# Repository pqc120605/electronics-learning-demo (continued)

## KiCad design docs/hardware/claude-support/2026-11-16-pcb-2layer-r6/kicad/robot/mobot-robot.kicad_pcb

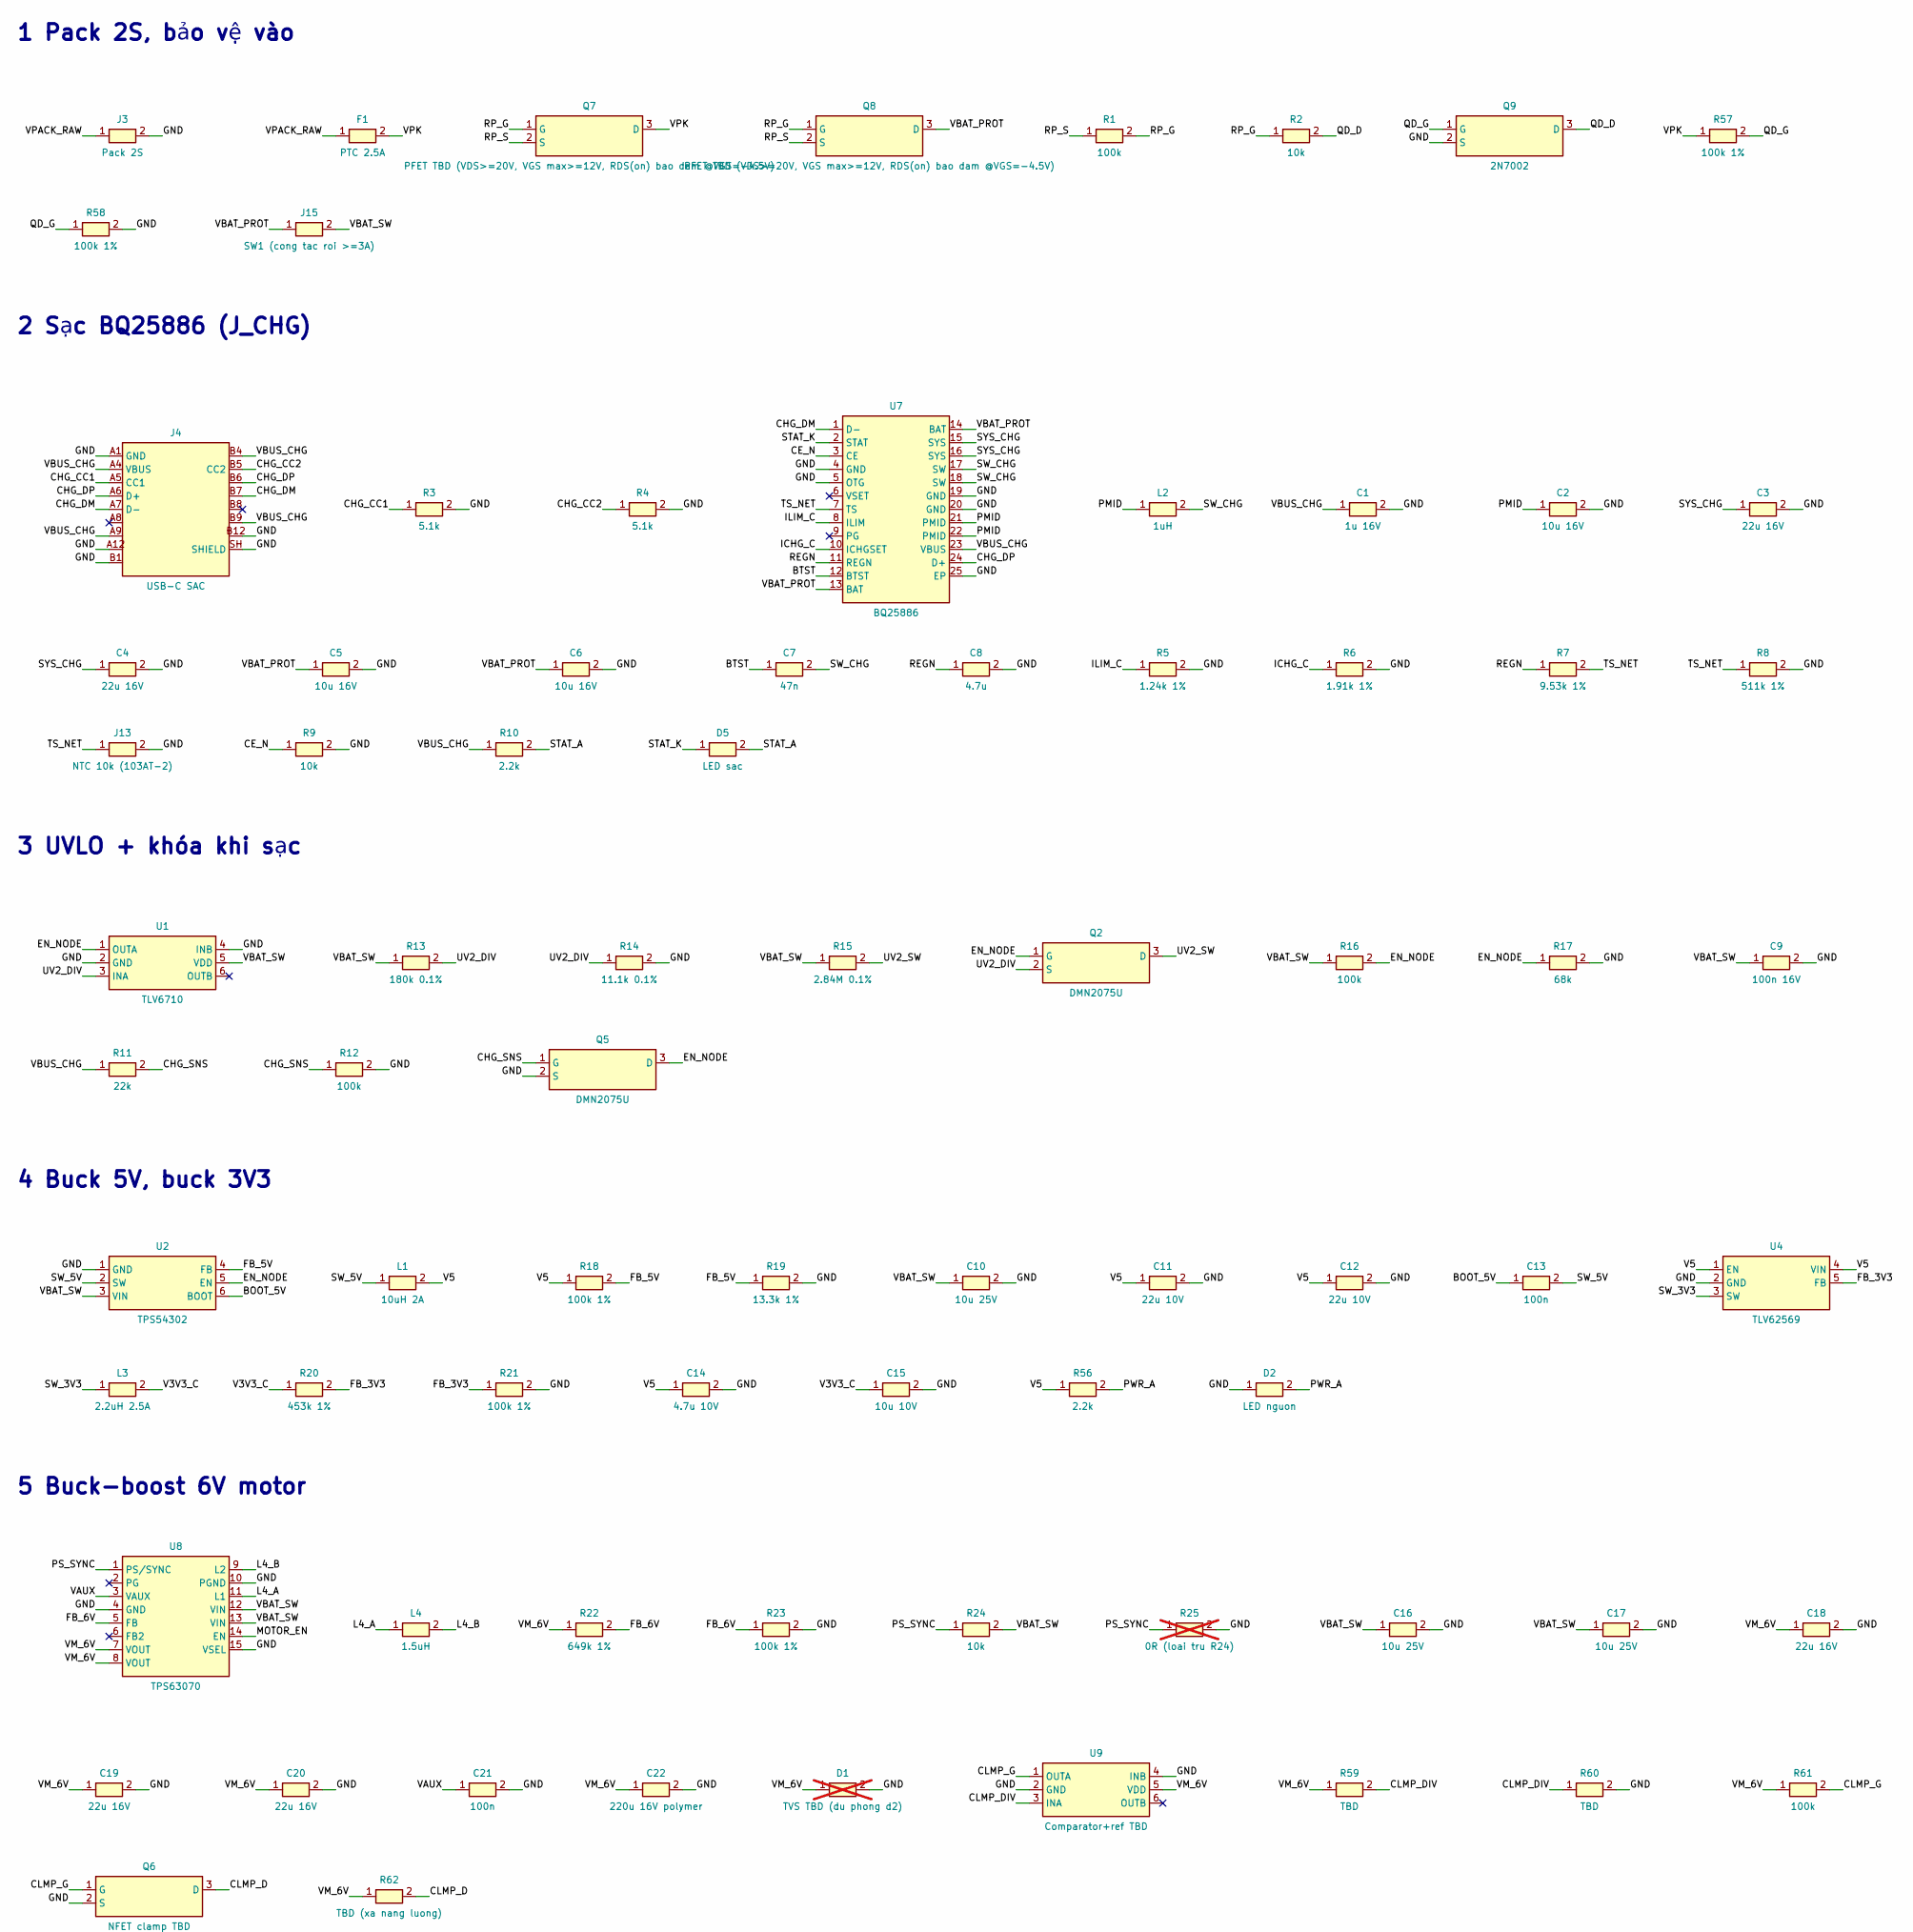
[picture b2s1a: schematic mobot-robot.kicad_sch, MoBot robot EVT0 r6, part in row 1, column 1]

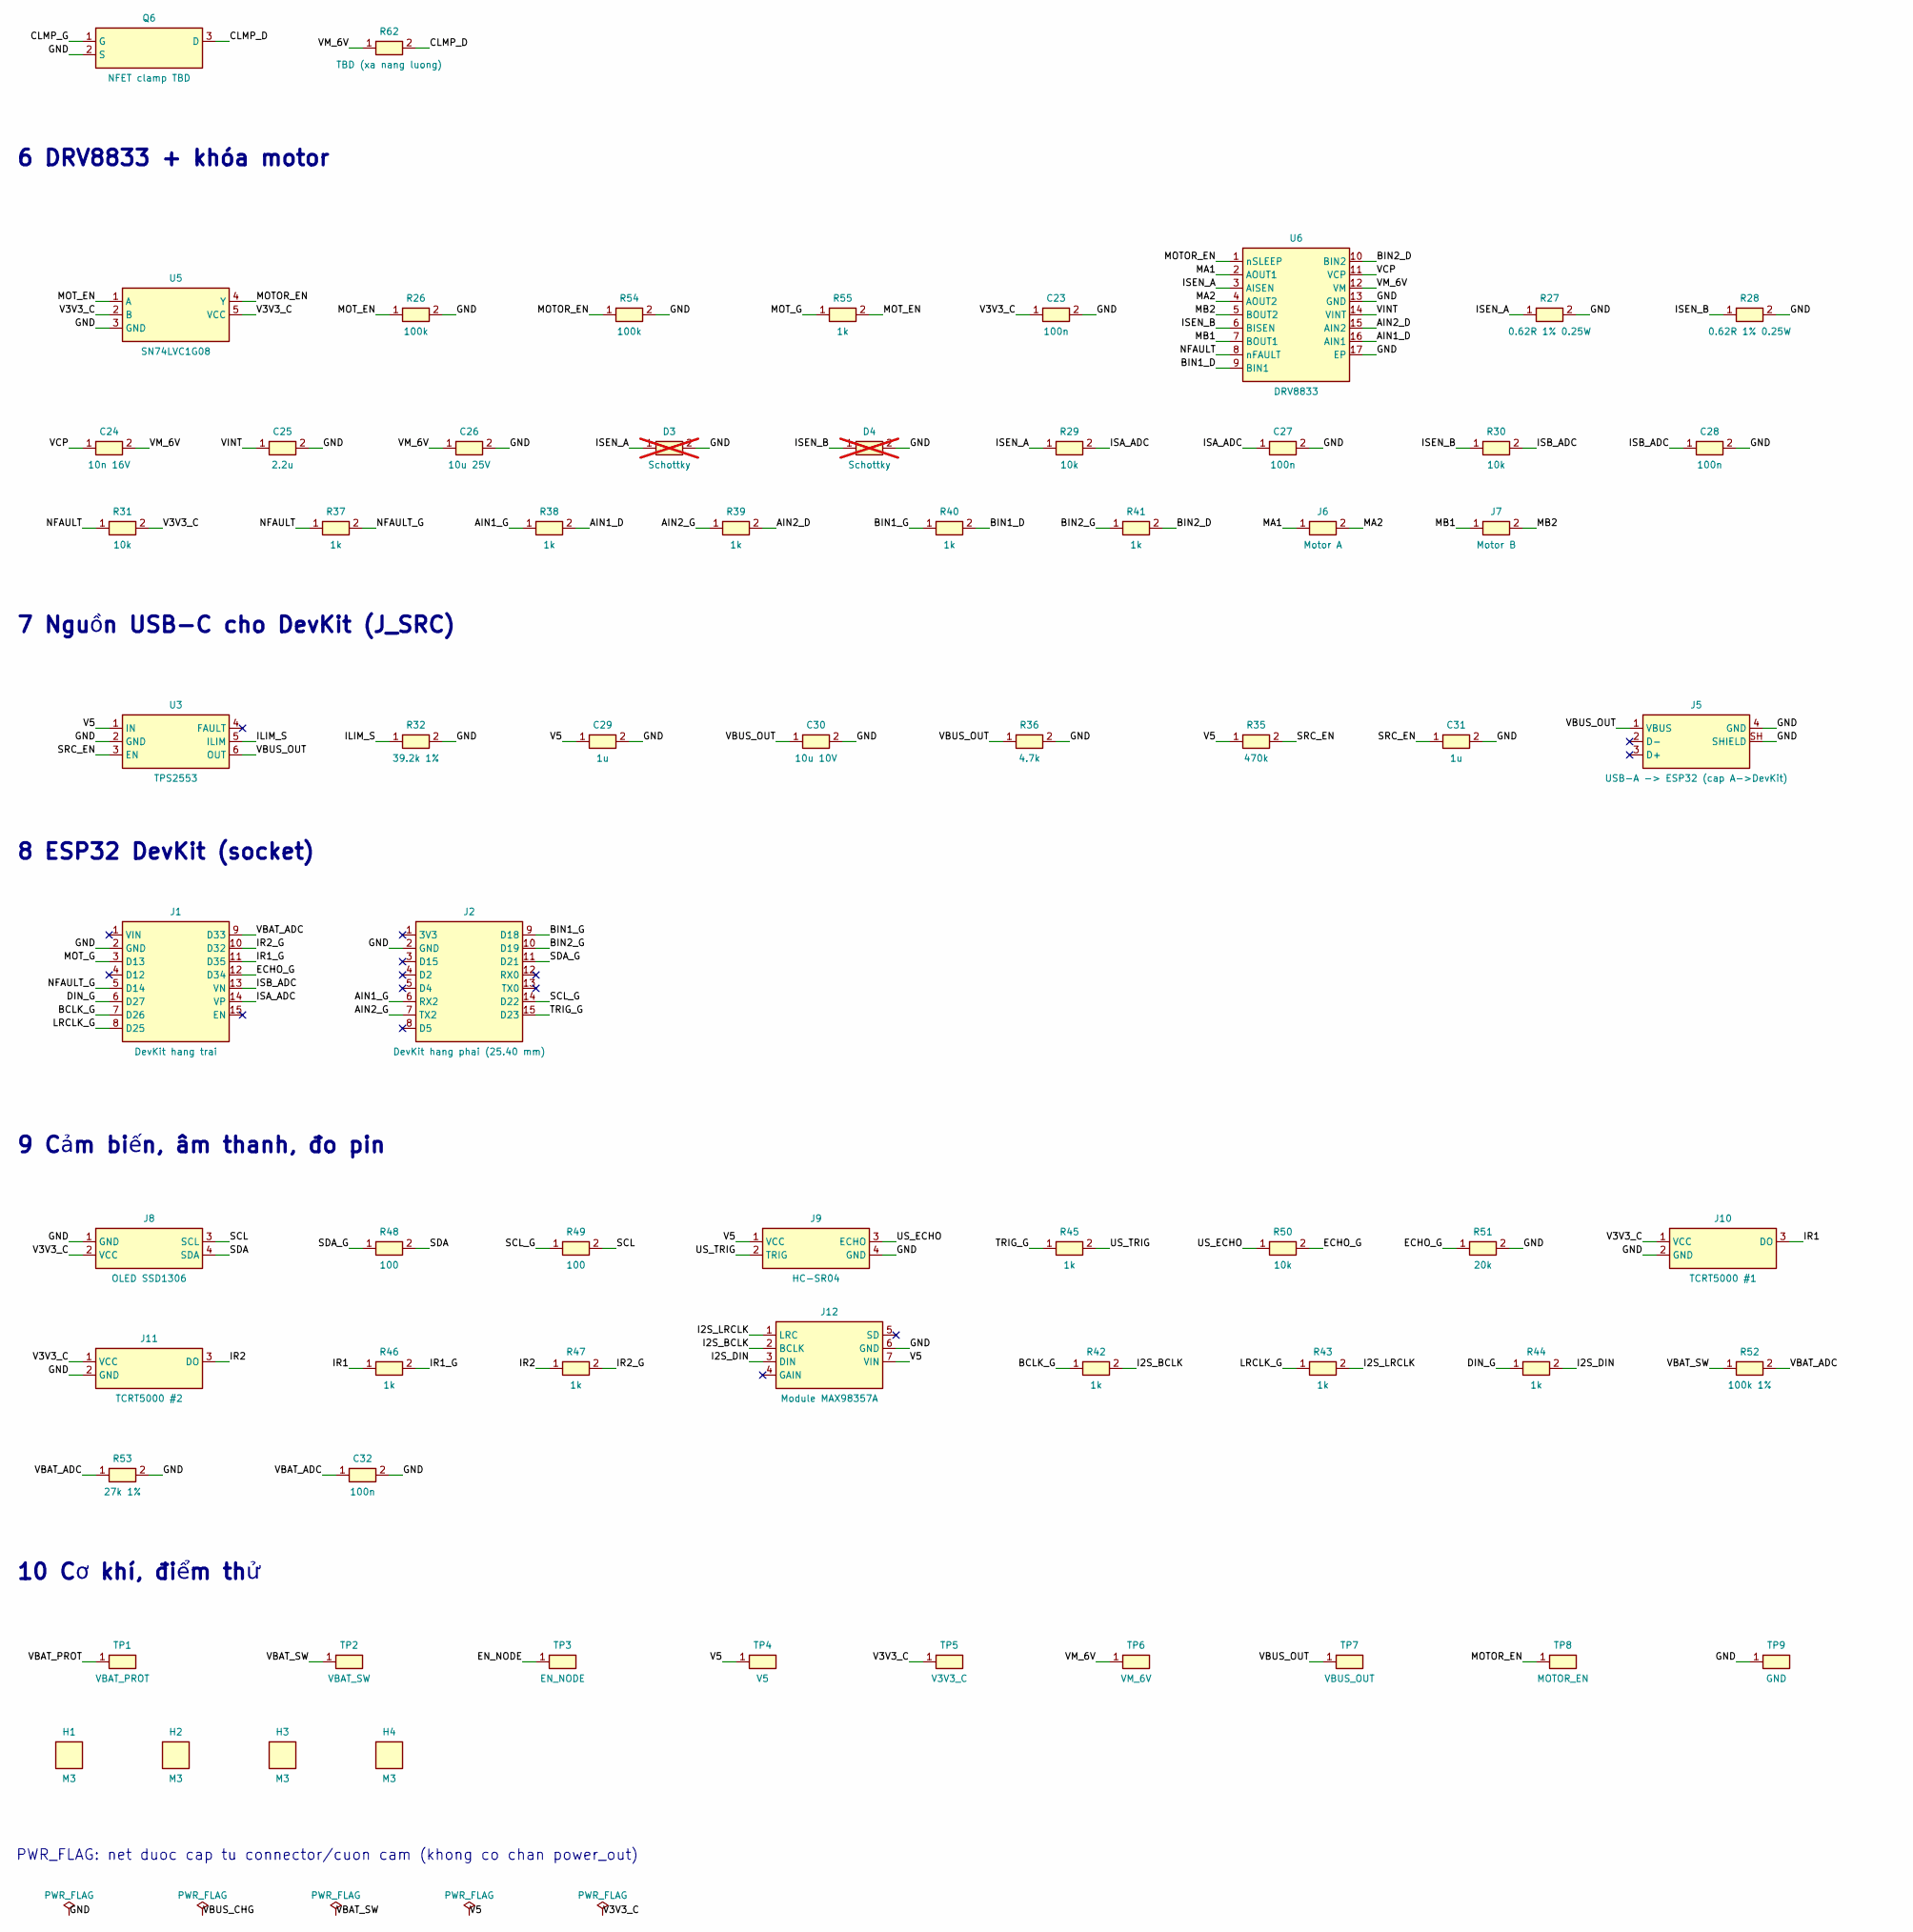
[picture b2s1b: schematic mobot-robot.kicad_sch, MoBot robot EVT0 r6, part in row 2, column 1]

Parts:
C1: 1u 16V; C_0603_1608Metric
C2, C5, C6: 10u 16V; C_0805_2012Metric
C3, C4, C18, C19, C20: 22u 16V; C_0805_2012Metric
C7: 47n; C_0603_1608Metric
C8: 4.7u; C_0603_1608Metric
C9: 100n 16V; C_0603_1608Metric
C10, C16, C17, C26: 10u 25V; C_0805_2012Metric
C11, C12: 22u 10V; C_0805_2012Metric
C13, C21, C23, C27, C28, C32: 100n; C_0603_1608Metric
C14: 4.7u 10V; C_0805_2012Metric
C15, C30: 10u 10V; C_0805_2012Metric
C22: 220u 16V polymer; CP_Elec_8x10
C24: 10n 16V; C_0603_1608Metric
C25: 2.2u; C_0603_1608Metric
C29, C31: 1u; C_0603_1608Metric
D1: TVS TBD (du phong d2); D_SMA; MPN TBD; not fitted
D2: LED nguon; LED_0603_1608Metric
D3, D4: Schottky; D_SOD-323; not fitted
D5: LED sac; LED_0603_1608Metric
F1: PTC 2.5A; Fuse_1812_4532Metric; MPN MF-MSMF250/16X
H1, H2, H3, H4: M3; MountingHole_3.2mm_M3
J1: DevKit hang trai; PinSocket_1x15_P2.54mm_Vertical
J2: DevKit hang phai (25.40 mm); PinSocket_1x15_P2.54mm_Vertical
J3: Pack 2S; JST_XH_B2B-XH-A_1x02_P2.50mm_Vertical; MPN B2B-XH-A
J4: USB-C SAC; USB_C_Receptacle_GCT_USB4105-xx-A_16P_TopMnt_Horizontal; MPN USB4105-GF-A
J5: USB-A -> ESP32 (cap A->DevKit); USB_A_Molex_67643_Horizontal; MPN Molex 67643 (suffix TBD)
J6: Motor A; JST_XH_B2B-XH-A_1x02_P2.50mm_Vertical; MPN B2B-XH-A
J7: Motor B; JST_XH_B2B-XH-A_1x02_P2.50mm_Vertical; MPN B2B-XH-A
J8: OLED SSD1306; PinSocket_1x04_P2.54mm_Vertical
J9: HC-SR04; PinSocket_1x04_P2.54mm_Vertical
J10: TCRT5000 #1; PinHeader_1x03_P2.54mm_Vertical
J11: TCRT5000 #2; PinHeader_1x03_P2.54mm_Vertical
J12: Module MAX98357A; PinSocket_1x07_P2.54mm_Vertical
J13: NTC 10k (103AT-2); JST_PH_B2B-PH-K_1x02_P2.00mm_Vertical; MPN B2B-PH-K-S
J15: SW1 (cong tac roi >=3A); JST_XH_B2B-XH-A_1x02_P2.50mm_Vertical; MPN B2B-XH-A
L1: 10uH 2A; L_Taiyo-Yuden_NR-50xx
L2: 1uH; L_Vishay_IHLP-2525; MPN IHLP2525CZER1R0M01
L3: 2.2uH 2.5A; L_Changjiang_FNR4030S
L4: 1.5uH; L_Changjiang_FNR4020S; MPN XFL4020-152ME
Q2, Q5: DMN2075U; SOT-23; MPN DMN2075U-7
Q6: NFET clamp TBD; SOT-23; MPN TBD
Q7, Q8: PFET TBD (VDS>=20V, VGS max>=12V, RDS(on) bao dam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; SOT-23; MPN TBD
Q9: 2N7002; SOT-23; MPN 2N7002
R1, R12, R16, R26, R54, R61: 100k; R_0603_1608Metric
R2, R9, R24, R29, R30, R31, R50: 10k; R_0603_1608Metric
R3, R4: 5.1k; R_0603_1608Metric
R5: 1.24k 1%; R_0603_1608Metric
R6: 1.91k 1%; R_0603_1608Metric
R7: 9.53k 1%; R_0603_1608Metric
R8: 511k 1%; R_0603_1608Metric
R10, R56: 2.2k; R_0603_1608Metric
R11: 22k; R_0603_1608Metric
R13: 180k 0.1%; R_0603_1608Metric
R14: 11.1k 0.1%; R_0603_1608Metric
R15: 2.84M 0.1%; R_0603_1608Metric
R17: 68k; R_0603_1608Metric
R18, R21, R23, R52, R57, R58: 100k 1%; R_0603_1608Metric
R19: 13.3k 1%; R_0603_1608Metric
R20: 453k 1%; R_0603_1608Metric
R22: 649k 1%; R_0603_1608Metric
R25: 0R (loai tru R24); R_0603_1608Metric; not fitted
R27, R28: 0.62R 1% 0.25W; R_1206_3216Metric
R32: 39.2k 1%; R_0603_1608Metric
R35: 470k; R_0603_1608Metric
R36: 4.7k; R_0603_1608Metric
R37, R38, R39, R40, R41, R42, R43, R44, R45, R46, R47, R55: 1k; R_0603_1608Metric
R48, R49: 100; R_0603_1608Metric
R51: 20k; R_0603_1608Metric
R53: 27k 1%; R_0603_1608Metric
R59, R60: TBD; R_0603_1608Metric
R62: TBD (xa nang luong); R_2512_6332Metric
TP1: VBAT_PROT; TestPoint_Pad_D1.5mm
TP2: VBAT_SW; TestPoint_Pad_D1.5mm
TP3: EN_NODE; TestPoint_Pad_D1.5mm
TP4: V5; TestPoint_Pad_D1.5mm
TP5: V3V3_C; TestPoint_Pad_D1.5mm
TP6: VM_6V; TestPoint_Pad_D1.5mm
TP7: VBUS_OUT; TestPoint_Pad_D1.5mm
TP8: MOTOR_EN; TestPoint_Pad_D1.5mm
TP9: GND; TestPoint_Pad_D1.5mm
U1: TLV6710; TSOT-23-6; MPN TLV6710DDCR
U2: TPS54302; SOT-23-6; MPN TPS54302DDCR
U3: TPS2553; SOT-23-6; MPN TPS2553DBVR
U4: TLV62569; SOT-23-5; MPN TLV62569DBVR
U5: SN74LVC1G08; SOT-23-5; MPN SN74LVC1G08DBVR
U6: DRV8833; HTSSOP-16-1EP_4.4x5mm_P0.65mm_EP3.4x5mm_Mask2.46x2.31mm; MPN DRV8833PWPR
U7: BQ25886; VQFN-24-1EP_4x4mm_P0.5mm_EP2.45x2.45mm; MPN BQ25886RGER
U8: TPS63070; Texas_RNM0015A_VQFN-15_2.5x3mm; MPN TPS63070RNMR
U9: Comparator+ref TBD; TSOT-23-6; MPN TBD

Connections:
/AIN1_D: R38.2, U6.16 (AIN1)
/AIN1_G: J2.6 (RX2), R38.1
/AIN2_D: R39.2, U6.15 (AIN2)
/AIN2_G: J2.7 (TX2), R39.1
/BCLK_G: J1.7 (D26), R42.1
/BIN1_D: R40.2, U6.9 (BIN1)
/BIN1_G: J2.9 (D18), R40.1
/BIN2_D: R41.2, U6.10 (BIN2)
/BIN2_G: J2.10 (D19), R41.1
/BOOT_5V: C13.1, U2.6 (BOOT)
/BTST: C7.1, U7.12 (BTST)
/CE_N: R9.1, U7.3 (CE)
/CHG_CC1: J4.A5 (CC1), R3.1
/CHG_CC2: J4.B5 (CC2), R4.1
/CHG_DM: J4.A7 (D-), J4.B7, U7.1 (D-)
/CHG_DP: J4.A6 (D+), J4.B6, U7.24 (D+)
/CHG_SNS: Q5.1 (G), R11.2, R12.1
/CLMP_D: Q6.3 (D), R62.2
/CLMP_DIV: R59.2, R60.1, U9.3 (INA)
/CLMP_G: Q6.1 (G), R61.2, U9.1 (OUTA)
/DIN_G: J1.6 (D27), R44.1
/ECHO_G: J1.12 (D34), R50.2, R51.1
/EN_NODE: Q2.1 (G), Q5.3 (D), R16.2, R17.1, TP3.1, U1.1 (OUTA), U2.5 (EN)
/FB_3V3: R20.2, R21.1, U4.5 (FB)
/FB_5V: R18.2, R19.1, U2.4 (FB)
/FB_6V: R22.2, R23.1, U8.5 (FB)
/GND: C1.2, C2.2, C3.2, C4.2, C5.2, C6.2, C8.2, C9.2, C10.2, C11.2, C12.2, C14.2, C15.2, C16.2, C17.2, C18.2, C19.2, C20.2, C21.2, C22.2 (-), C23.2, C25.2, C26.2, C27.2, C28.2, C29.2, C30.2, C31.2, C32.2, D1.2 (A), D2.1 (K), D3.2 (A), D4.2 (A), J1.2 (GND), J2.2 (GND), J3.2 (-), J4.A1 (GND), J4.A12, J4.B1, J4.B12, J4.SH (SHIELD), J5.4 (GND), J5.SH (SHIELD), J8.1 (GND), J9.4 (GND), J10.2 (GND), J11.2 (GND), J12.6 (GND), J13.2, Q5.2 (S), Q6.2 (S), Q9.2 (S), R3.2, R4.2, R5.2, R6.2, R8.2, R9.2, R12.2, R14.2, R17.2, R19.2, R21.2, R23.2, R25.2, R26.2, R27.2, R28.2, R32.2, R36.2, R51.2, R53.2, R54.2, R58.2, R60.2, TP9.1, U1.2 (GND), U1.4 (INB), U2.1 (GND), U3.2 (GND), U4.2 (GND), U5.3 (GND), U6.13 (GND), U6.17 (EP), U7.4 (GND), U7.5 (OTG), U7.19 (GND), U7.20 (GND), U7.25 (EP), U8.4 (GND), U8.10 (PGND), U8.15 (VSEL), U9.2 (GND), U9.4 (INB)
/I2S_BCLK: J12.2 (BCLK), R42.2
/I2S_DIN: J12.3 (DIN), R44.2
/I2S_LRCLK: J12.1 (LRC), R43.2
/ICHG_C: R6.1, U7.10 (ICHGSET)
/ILIM_C: R5.1, U7.8 (ILIM)
/ILIM_S: R32.1, U3.5 (ILIM)
/IR1: J10.3 (DO), R46.1
/IR1_G: J1.11 (D35), R46.2
/IR2: J11.3 (DO), R47.1
/IR2_G: J1.10 (D32), R47.2
/ISA_ADC: C27.1, J1.14 (VP), R29.2
/ISB_ADC: C28.1, J1.13 (VN), R30.2
/ISEN_A: D3.1 (K), R27.1, R29.1, U6.3 (AISEN)
/ISEN_B: D4.1 (K), R28.1, R30.1, U6.6 (BISEN)
/L4_A: L4.1, U8.11 (L1)
/L4_B: L4.2, U8.9 (L2)
/LRCLK_G: J1.8 (D25), R43.1
/MA1: J6.1, U6.2 (AOUT1)
/MA2: J6.2, U6.4 (AOUT2)
/MB1: J7.1, U6.7 (BOUT1)
/MB2: J7.2, U6.5 (BOUT2)
/MOTOR_EN: R54.1, TP8.1, U5.4 (Y), U6.1 (nSLEEP), U8.14 (EN)
/MOT_EN: R26.1, R55.2, U5.1 (A)
/MOT_G: J1.3 (D13), R55.1
/NFAULT: R31.1, R37.1, U6.8 (nFAULT)
/NFAULT_G: J1.5 (D14), R37.2
/PMID: C2.1, L2.1, U7.21 (PMID), U7.22 (PMID)
/PS_SYNC: R24.1, R25.1, U8.1 (PS/SYNC)
/PWR_A: D2.2 (A), R56.2
/QD_D: Q9.3 (D), R2.2
/QD_G: Q9.1 (G), R57.2, R58.1
/REGN: C8.1, R7.1, U7.11 (REGN)
/RP_G: Q7.1 (G), Q8.1 (G), R1.2, R2.1
/RP_S: Q7.2 (S), Q8.2 (S), R1.1
/SCL: J8.3 (SCL), R49.2
/SCL_G: J2.14 (D22), R49.1
/SDA: J8.4 (SDA), R48.2
/SDA_G: J2.11 (D21), R48.1
/SRC_EN: C31.1, R35.2, U3.3 (EN)
/STAT_A: D5.2 (A), R10.2
/STAT_K: D5.1 (K), U7.2 (STAT)
/SW_3V3: L3.1, U4.3 (SW)
/SW_5V: C13.2, L1.1, U2.2 (SW)
/SW_CHG: C7.2, L2.2, U7.17 (SW), U7.18 (SW)
/SYS_CHG: C3.1, C4.1, U7.15 (SYS), U7.16 (SYS)
/TRIG_G: J2.15 (D23), R45.1
/TS_NET: J13.1, R7.2, R8.1, U7.7 (TS)
/US_ECHO: J9.3 (ECHO), R50.1
/US_TRIG: J9.2 (TRIG), R45.2
/UV2_DIV: Q2.2 (S), R13.2, R14.1, U1.3 (INA)
/UV2_SW: Q2.3 (D), R15.2
/V3V3_C: C15.1, C23.1, J8.2 (VCC), J10.1 (VCC), J11.1 (VCC), L3.2, R20.1, R31.2, TP5.1, U5.2 (B), U5.5 (VCC)
/V5: C11.1, C12.1, C14.1, C29.1, J9.1 (VCC), J12.7 (VIN), L1.2, R18.1, R35.1, R56.1, TP4.1, U3.1 (IN), U4.1 (EN), U4.4 (VIN)
/VAUX: C21.1, U8.3 (VAUX)
/VBAT_ADC: C32.1, J1.9 (D33), R52.2, R53.1
/VBAT_PROT: C5.1, C6.1, J15.1 (IN), Q8.3 (D), TP1.1, U7.13 (BAT), U7.14 (BAT)
/VBAT_SW: C9.1, C10.1, C16.1, C17.1, J15.2 (OUT), R13.1, R15.1, R16.1, R24.2, R52.1, TP2.1, U1.5 (VDD), U2.3 (VIN), U8.12 (VIN), U8.13 (VIN)
/VBUS_CHG: C1.1, J4.A4 (VBUS), J4.A9, J4.B4, J4.B9, R10.1, R11.1, U7.23 (VBUS)
/VBUS_OUT: C30.1, J5.1 (VBUS), R36.1, TP7.1, U3.6 (OUT)
/VCP: C24.1, U6.11 (VCP)
/VINT: C25.1, U6.14 (VINT)
/VM_6V: C18.1, C19.1, C20.1, C22.1 (+), C24.2, C26.1, D1.1 (K), R22.1, R59.1, R61.1, R62.1, TP6.1, U6.12 (VM), U8.7 (VOUT), U8.8 (VOUT), U9.5 (VDD)
/VPACK_RAW: F1.1, J3.1 (+)
/VPK: F1.2, Q7.3 (D), R57.1

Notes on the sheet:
1 Pack 2S, bảo vệ vào
2 Sạc BQ25886 (J_CHG)
3 UVLO + khóa khi sạc
4 Buck 5V, buck 3V3
5 Buck-boost 6V motor
6 DRV8833 + khóa motor
7 Nguồn USB-C cho DevKit (J_SRC)
8 ESP32 DevKit (socket)
9 Cảm biến, âm thanh, đo pin
10 Cơ khí, điểm thử
PWR_FLAG: net duoc cap tu connector/cuon cam (khong co chan power_out)

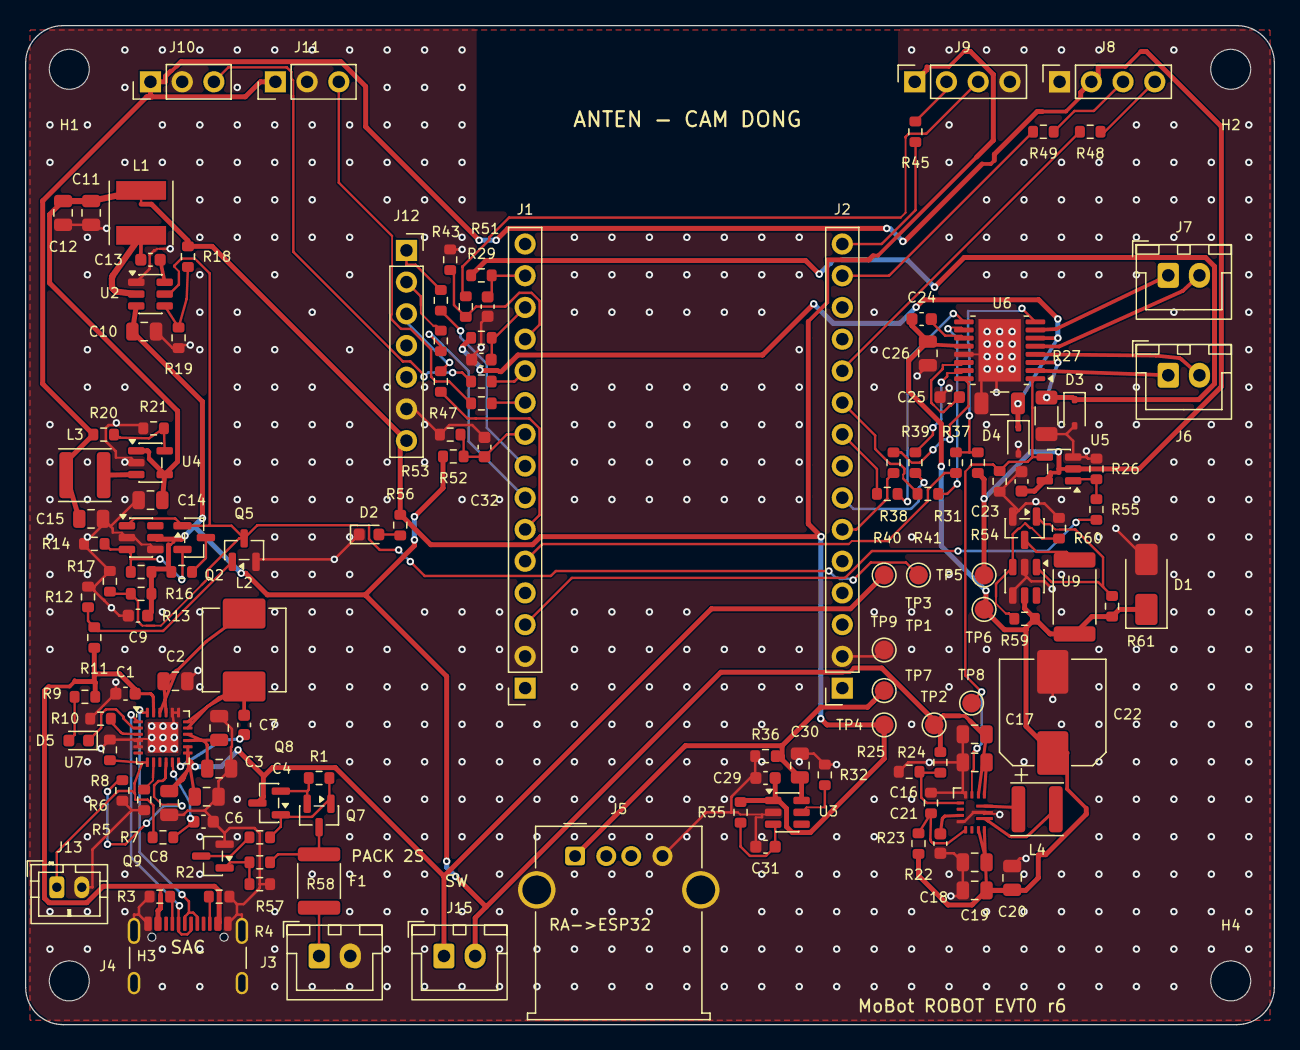
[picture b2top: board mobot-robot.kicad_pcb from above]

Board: 2 copper layers, 100.0 x 80.0 mm, 144 parts (0 on the bottom side), 91 nets.

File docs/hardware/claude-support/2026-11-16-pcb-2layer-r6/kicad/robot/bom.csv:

"Reference","Value","Footprint","MPN","QUANTITY","DNP"
"C1","1u 16V","Capacitor_SMD:C_0603_1608Metric","","1",""
"C2,C5,C6","10u 16V","Capacitor_SMD:C_0805_2012Metric","","3",""
"C3,C4,C18-C20","22u 16V","Capacitor_SMD:C_0805_2012Metric","","5",""
"C7","47n","Capacitor_SMD:C_0603_1608Metric","","1",""
"C8","4.7u","Capacitor_SMD:C_0603_1608Metric","","1",""
"C9","100n 16V","Capacitor_SMD:C_0603_1608Metric","","1",""
"C10,C16,C17,C26","10u 25V","Capacitor_SMD:C_0805_2012Metric","","4",""
"C11,C12","22u 10V","Capacitor_SMD:C_0805_2012Metric","","2",""
"C13,C21,C23,C27,C28,C32","100n","Capacitor_SMD:C_0603_1608Metric","","6",""
"C14","4.7u 10V","Capacitor_SMD:C_0805_2012Metric","","1",""
"C15,C30","10u 10V","Capacitor_SMD:C_0805_2012Metric","","2",""
"C22","220u 16V polymer","Capacitor_SMD:CP_Elec_8x10","","1",""
"C24","10n 16V","Capacitor_SMD:C_0603_1608Metric","","1",""
"C25","2.2u","Capacitor_SMD:C_0603_1608Metric","","1",""
"C29,C31","1u","Capacitor_SMD:C_0603_1608Metric","","2",""
"D1","TVS TBD (du phong d2)","Diode_SMD:D_SMA","TBD","1","DNP"
"D2","LED nguon","LED_SMD:LED_0603_1608Metric","","1",""
"D3,D4","Schottky","Diode_SMD:D_SOD-323","","2","DNP"
"D5","LED sac","LED_SMD:LED_0603_1608Metric","","1",""
"F1","PTC 2.5A","Fuse:Fuse_1812_4532Metric","MF-MSMF250/16X","1",""
"J1","DevKit hang trai","Connector_PinSocket_2.54mm:PinSocket_1x15_P2.54mm_Vertical","","1",""
"J2","DevKit hang phai (25.40 mm)","Connector_PinSocket_2.54mm:PinSocket_1x15_P2.54mm_Vertical","","1",""
"J3","Pack 2S","Connector_JST:JST_XH_B2B-XH-A_1x02_P2.50mm_Vertical","B2B-XH-A","1",""
"J4","USB-C SAC","Connector_USB:USB_C_Receptacle_GCT_USB4105-xx-A_16P_TopMnt_Horizontal","USB4105-GF-A","1",""
"J5","USB-A -> ESP32 (cap A->DevKit)","Connector_USB:USB_A_Molex_67643_Horizontal","Molex 67643 (suffix TBD)","1",""
"J6","Motor A","Connector_JST:JST_XH_B2B-XH-A_1x02_P2.50mm_Vertical","B2B-XH-A","1",""
"J7","Motor B","Connector_JST:JST_XH_B2B-XH-A_1x02_P2.50mm_Vertical","B2B-XH-A","1",""
"J8","OLED SSD1306","Connector_PinSocket_2.54mm:PinSocket_1x04_P2.54mm_Vertical","","1",""
"J9","HC-SR04","Connector_PinSocket_2.54mm:PinSocket_1x04_P2.54mm_Vertical","","1",""
"J10","TCRT5000 #1","Connector_PinHeader_2.54mm:PinHeader_1x03_P2.54mm_Vertical","","1",""
"J11","TCRT5000 #2","Connector_PinHeader_2.54mm:PinHeader_1x03_P2.54mm_Vertical","","1",""
"J12","Module MAX98357A","Connector_PinSocket_2.54mm:PinSocket_1x07_P2.54mm_Vertical","","1",""
"J13","NTC 10k (103AT-2)","Connector_JST:JST_PH_B2B-PH-K_1x02_P2.00mm_Vertical","B2B-PH-K-S","1",""
"J15","SW1 (cong tac roi >=3A)","Connector_JST:JST_XH_B2B-XH-A_1x02_P2.50mm_Vertical","B2B-XH-A","1",""
"L1","10uH 2A","Inductor_SMD:L_Taiyo-Yuden_NR-50xx","","1",""
"L2","1uH","Inductor_SMD:L_Vishay_IHLP-2525","IHLP2525CZER1R0M01","1",""
"L3","2.2uH 2.5A","Inductor_SMD:L_Changjiang_FNR4030S","","1",""
"L4","1.5uH","Inductor_SMD:L_Changjiang_FNR4020S","XFL4020-152ME","1",""
"Q2,Q5","DMN2075U","Package_TO_SOT_SMD:SOT-23","DMN2075U-7","2",""
"Q6","NFET clamp TBD","Package_TO_SOT_SMD:SOT-23","TBD","1",""
"Q7,Q8","PFET TBD (VDS>=20V, VGS max>=12V, RDS(on) bao dam @VGS=-4.5V)","Package_TO_SOT_SMD:SOT-23","TBD","2",""
"Q9","2N7002","Package_TO_SOT_SMD:SOT-23","2N7002","1",""
"R1,R12,R16,R26,R54,R61","100k","Resistor_SMD:R_0603_1608Metric","","6",""
"R2,R9,R24,R29-R31,R50","10k","Resistor_SMD:R_0603_1608Metric","","7",""
"R3,R4","5.1k","Resistor_SMD:R_0603_1608Metric","","2",""
"R5","1.24k 1%","Resistor_SMD:R_0603_1608Metric","","1",""
"R6","1.91k 1%","Resistor_SMD:R_0603_1608Metric","","1",""
"R7","9.53k 1%","Resistor_SMD:R_0603_1608Metric","","1",""
"R8","511k 1%","Resistor_SMD:R_0603_1608Metric","","1",""
"R10,R56","2.2k","Resistor_SMD:R_0603_1608Metric","","2",""
"R11","22k","Resistor_SMD:R_0603_1608Metric","","1",""
"R13","180k 0.1%","Resistor_SMD:R_0603_1608Metric","","1",""
"R14","11.1k 0.1%","Resistor_SMD:R_0603_1608Metric","","1",""
"R15","2.84M 0.1%","Resistor_SMD:R_0603_1608Metric","","1",""
"R17","68k","Resistor_SMD:R_0603_1608Metric","","1",""
"R18,R21,R23,R52,R57,R58","100k 1%","Resistor_SMD:R_0603_1608Metric","","6",""
"R19","13.3k 1%","Resistor_SMD:R_0603_1608Metric","","1",""
"R20","453k 1%","Resistor_SMD:R_0603_1608Metric","","1",""
"R22","649k 1%","Resistor_SMD:R_0603_1608Metric","","1",""
"R25","0R (loai tru R24)","Resistor_SMD:R_0603_1608Metric","","1","DNP"
"R27,R28","0.62R 1% 0.25W","Resistor_SMD:R_1206_3216Metric","","2",""
"R32","39.2k 1%","Resistor_SMD:R_0603_1608Metric","","1",""
"R35","470k","Resistor_SMD:R_0603_1608Metric","","1",""
"R36","4.7k","Resistor_SMD:R_0603_1608Metric","","1",""
"R37-R47,R55","1k","Resistor_SMD:R_0603_1608Metric","","12",""
"R48,R49","100","Resistor_SMD:R_0603_1608Metric","","2",""
"R51","20k","Resistor_SMD:R_0603_1608Metric","","1",""
"R53","27k 1%","Resistor_SMD:R_0603_1608Metric","","1",""
"R59,R60","TBD","Resistor_SMD:R_0603_1608Metric","","2",""
"R62","TBD (xa nang luong)","Resistor_SMD:R_2512_6332Metric","","1",""
"U1","TLV6710","Package_TO_SOT_SMD:TSOT-23-6","TLV6710DDCR","1",""
"U2","TPS54302","Package_TO_SOT_SMD:SOT-23-6","TPS54302DDCR","1",""
"U3","TPS2553","Package_TO_SOT_SMD:SOT-23-6","TPS2553DBVR","1",""
"U4","TLV62569","Package_TO_SOT_SMD:SOT-23-5","TLV62569DBVR","1",""
"U5","SN74LVC1G08","Package_TO_SOT_SMD:SOT-23-5","SN74LVC1G08DBVR","1",""
"U6","DRV8833","Package_SO:HTSSOP-16-1EP_4.4x5mm_P0.65mm_EP3.4x5mm_Mask2.46x2.31mm","DRV8833PWPR","1",""
"U7","BQ25886","Package_DFN_QFN:VQFN-24-1EP_4x4mm_P0.5mm_EP2.45x2.45mm","BQ25886RGER","1",""
"U8","TPS63070","mobot:Texas_RNM0015A_VQFN-15_2.5x3mm","TPS63070RNMR","1",""
"U9","Comparator+ref TBD","Package_TO_SOT_SMD:TSOT-23-6","TBD","1",""

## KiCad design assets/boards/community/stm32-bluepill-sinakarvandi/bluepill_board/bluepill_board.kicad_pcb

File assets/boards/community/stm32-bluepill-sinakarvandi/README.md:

# PCB Designs

My random PCB designs using [KiCad](https://www.kicad.org/).

- **Blue Pill Board**

  Custom PCB design for STM32 "Blue Pill" development board.

- **ESP32-S3 Board**

  Schematic and layout for ESP32-S3-based design.

- **ESP32 WROOM Board**

  PCB based on ESP32-WROOM module.

- **LED Blinker**

  Simple circuit for testing LEDs and basic PCB workflow.

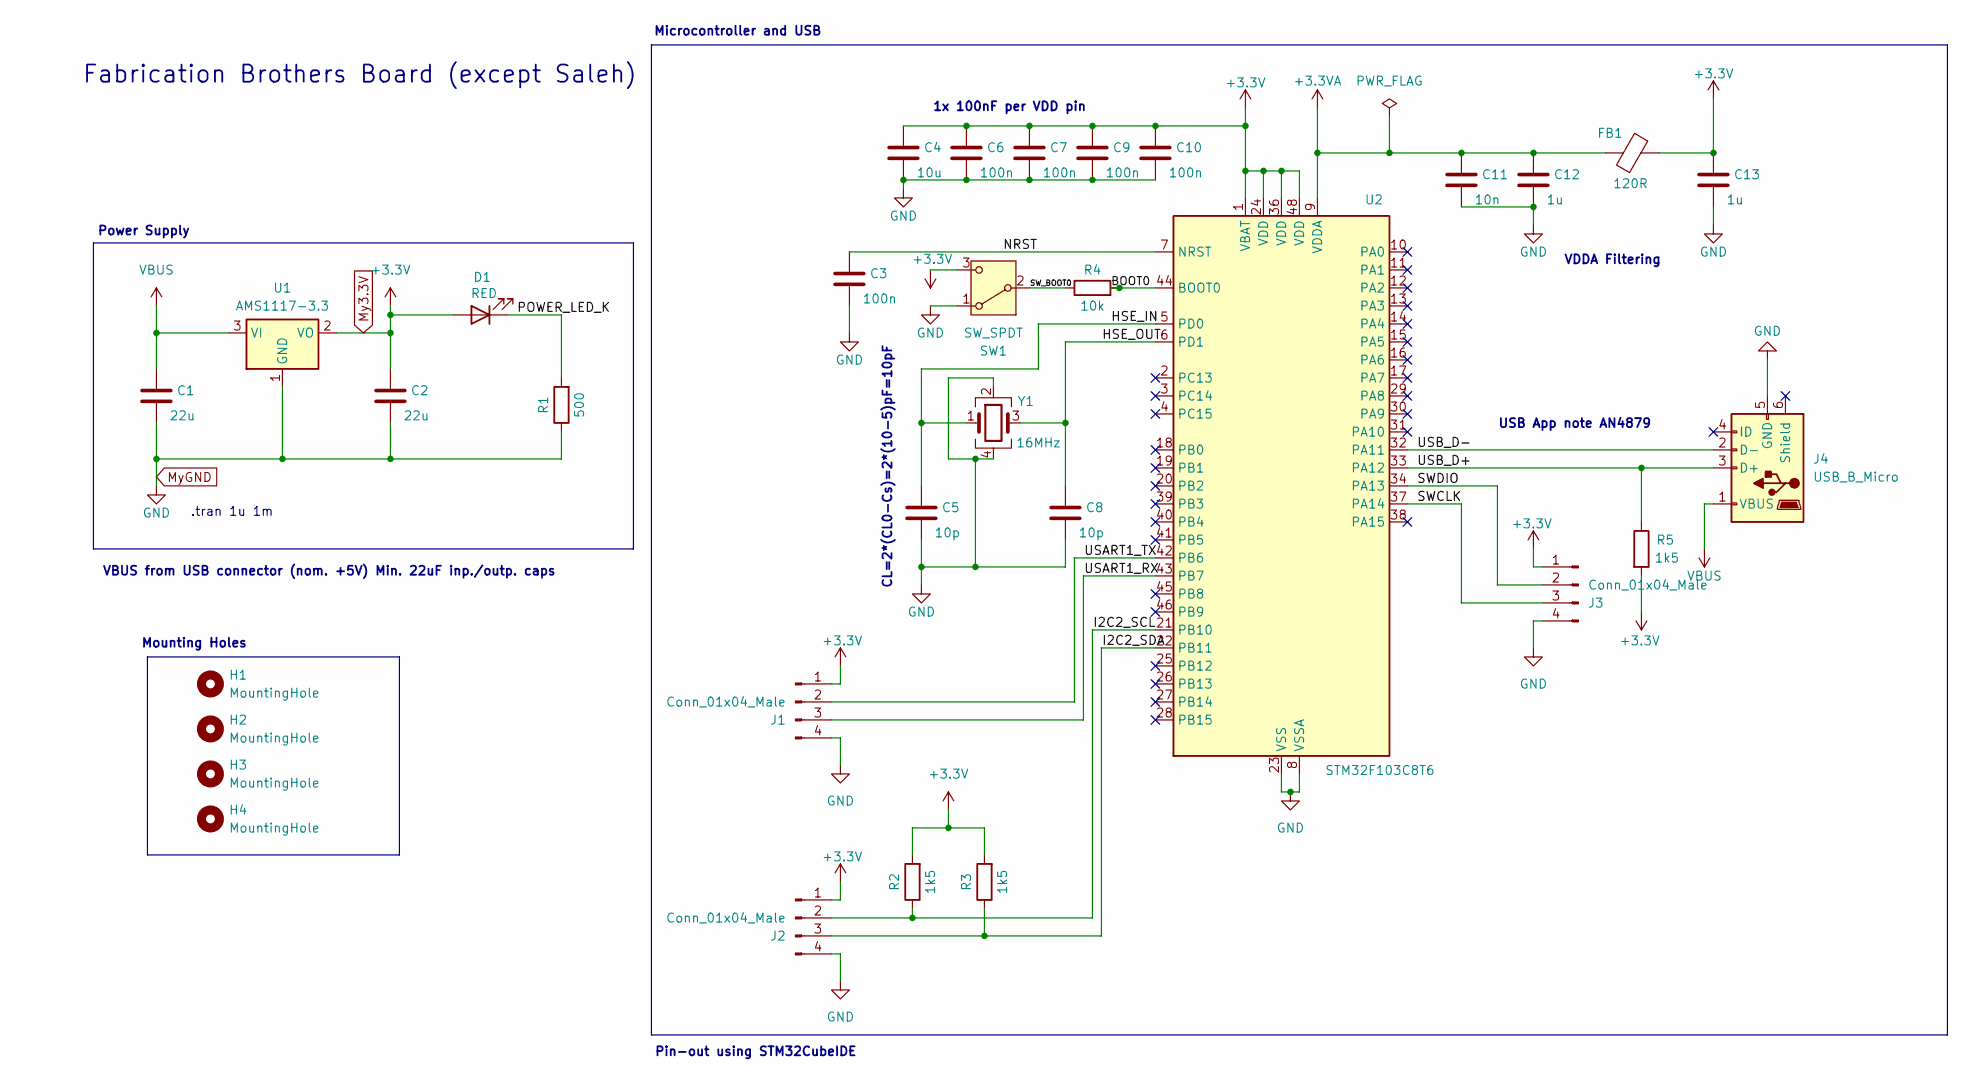
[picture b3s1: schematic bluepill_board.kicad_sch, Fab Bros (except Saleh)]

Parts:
C1, C2: 22u; C_0805_2012Metric; LCSC C296720
C3, C6, C7, C9, C10: 100n; C_0402_1005Metric; LCSC C1525
C4: 10u; C_0603_1608Metric; LCSC C19702
C5, C8: 10p; C_0402_1005Metric; LCSC C32949
C11: 10n; C_0402_1005Metric; LCSC C15195
C12, C13: 1u; C_0402_1005Metric; LCSC C29266
D1: RED; LED_0603_1608Metric; LCSC C7371906
FB1: 120R; L_0603_1608Metric; LCSC C14709
H1, H2, H3, H4: MountingHole; MountingHole_2.2mm_M2
J1, J2, J3: Conn_01x04_Male; PinHeader_1x04_P2.54mm_Vertical; LCSC C2337
J4: USB_B_Micro; USB_Micro-B_Wuerth_629105150521; LCSC C2894326
R1: 500; R_0402_1005Metric; LCSC C25109
R2, R3, R5: 1k5; R_0402_1005Metric; LCSC C25867
R4: 10k; R_0402_1005Metric; LCSC C25744
SW1: SW_SPDT; SW_SPDT_PCM12; LCSC C221841
U1: AMS1117-3.3; SOT-223-3_TabPin2; LCSC C6186
U2: STM32F103C8T6; LQFP-48_7x7mm_P0.5mm; LCSC C8734
Y1: 16MHz; Crystal_SMD_3225-4Pin_3.2x2.5mm; LCSC C518160

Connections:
+3.3V: C2.1, C4.1, C6.1, C7.1, C9.1, C10.1, C13.1, D1.2 (A), FB1.2, J1.1, J2.1, J3.1, R2.2, R3.2, R5.2, SW1.3 (C), U1.2 (VO), U2.1 (VBAT), U2.24 (VDD), U2.36 (VDD), U2.48 (VDD)
+3.3VA: C11.1, C12.1, FB1.1, U2.9 (VDDA)
/BOOT0: R4.2, U2.44 (BOOT0)
/HSE_IN: C5.1, U2.5 (PD0), Y1.1
/HSE_OUT: C8.1, U2.6 (PD1), Y1.3
/I2C2_SCL: J2.2, R2.1, U2.21 (PB10)
/I2C2_SDA: J2.3, R3.1, U2.22 (PB11)
/NRST: C3.1, U2.7 (NRST)
/POWER_LED_K: D1.1 (K), R1.2
/SWCLK: J3.3, U2.37 (PA14)
/SWDIO: J3.2, U2.34 (PA13)
/SW_BOOT0: R4.1, SW1.2 (B)
/USART1_RX: J1.3, U2.43 (PB7)
/USART1_TX: J1.2, U2.42 (PB6)
/USB_D+: J4.3 (D+), R5.1, U2.33 (PA12)
/USB_D-: J4.2 (D-), U2.32 (PA11)
GND: C1.2, C2.2, C3.2, C4.2, C5.2, C6.2, C7.2, C8.2, C9.2, C10.2, C11.2, C12.2, C13.2, J1.4, J2.4, J3.4, J4.5 (GND), R1.1, SW1.1 (A), U1.1 (GND), U2.8 (VSSA), U2.23 (VSS), U2.35 (VSS), U2.47 (VSS), Y1.2, Y1.4
VBUS: C1.1, J4.1 (VBUS), U1.3 (VI)

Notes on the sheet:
CL=2*(CL0-Cs)=2*(10-5)pF=10pF
Pin-out using STM32CubeIDE
Mounting Holes
VBUS from USB connector (nom. +5V) Min. 22uF inp./outp. caps
Fabrication Brothers Board (except Saleh)
Power Supply
VDDA Filtering
1x 100nF per VDD pin
USB App note AN4879
Microcontroller and USB
.tran 1u 1m

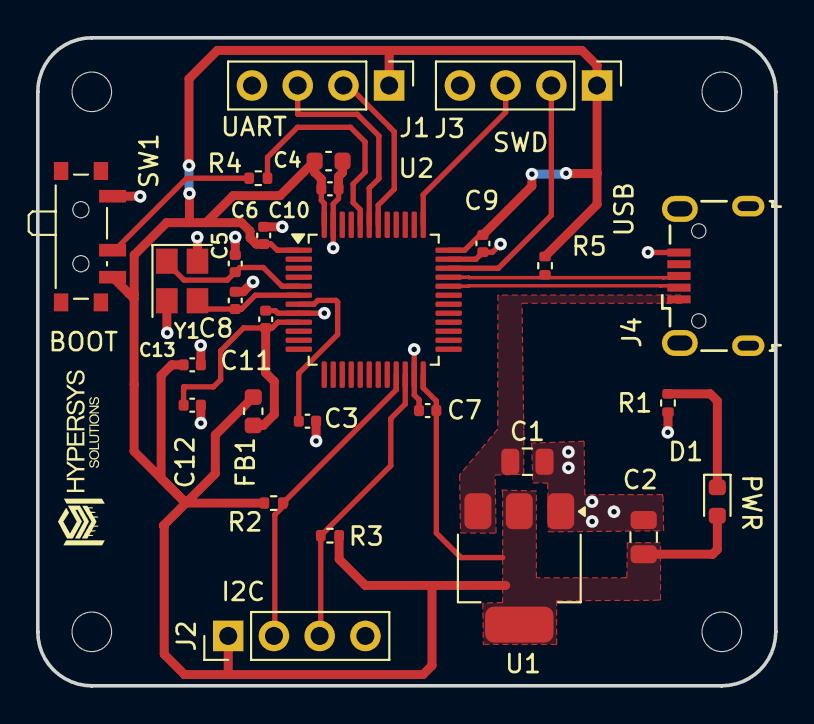
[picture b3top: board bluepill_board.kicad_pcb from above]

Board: 2 copper layers, 41.0 x 36.0 mm, 32 parts (0 on the bottom side), 18 nets.
